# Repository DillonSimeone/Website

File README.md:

# Dillon Simeone | Portfolio & Haptic Lab

A high-performance, modular portfolio showcasing innovation at the intersection of accessibility, haptics, and embedded engineering.

---

## Overview
This repository contains the source code for my portfolio website. More than just a static page, this project is a testbed for extreme performance optimization and modular content management. 

I am a **Deaf engineer, maker, and designer** specializing in haptic feedback systems and accessibility technology. This site reflects that multidisciplinary approach, combining sleek aesthetics with rigorous technical foundations.

### Key Features:
- **Modular Content Architecture**: Projects are managed as standalone HTML fragments in `src/content/`, dynamically injected via Handlebars.
- **Minification**: Powered by Vite and `vite-plugin-singlefile`, the entire production site is bundled into a single, highly-compressed `index.html`.
- **Shop**: A direct-to-maker storefront integrated with Stripe for hardware prototypes and art pieces.
- **Performance-First Background**: Uses static SVG "skeletons" with real-time color re-skinning to achieve 60FPS animations with ~0% CPU overhead.

---

## Tech Stack
- **Core**: HTML5, Vanilla JavaScript, CSS3
- **Build Engine**: [Vite](https://vitejs.dev/)
- **Templating**: Handlebars
- **Plugins**: 
  - `vite-plugin-singlefile`: Inlines all assets into one file for the final build.
  - `vite-plugin-handlebars`: Manages modular content injection and HMR.
  - `vite-plugin-minify`: Strips whitespace, comments, and console logs.
  - `Terser`: Advanced JS compression for production.

---

## Project Structure
- **`src/`**: Source files.
  - **`content/`**: Categorized project cards (`laser/`, `3dprinting/`, `esp32/`, `shop/`).
  - **`partials/`**: Reusable UI components like navigation and the hero section.
  - **`scripts/`**: Modular logic for theme management and animations.
  - **`styles/`**: Centralized CSS with theming variables.
- **`public/`**: Static assets, including mini-projects, images, and research PDFs.
- **`dist/`**: Automated production build output.
- **`legacy/`**: Preservation of original root files and background regeneration tools.

---

## Development

### Prerequisites
- [Node.js](https://nodejs.org/) (Latest LTS)
- NPM

### Commands
```bash
# Install dependencies
npm install

# Start local development server (with HMR)
npm run dev

# Generate production build (dist/index.html)
npm run build
```

### Content Generation
To add a new project or shop entry without manual boilerplate, use the provided utility:
```bash
.\CreateEntry.bat
```
Follow the prompts to select a category, and the script will generate a correctly formatted HTML fragment in the appropriate directory.

---

## Research & Accessibility
A core pillar of this portfolio is my work on the **GeLu (GestoLumina) Bracers** and the **PULSE Haptic Ecosystem**. These projects focus on universal music design and environmental awareness for the Deaf community. 

For more details, see the documentation in the **Work** and **Embedded** sections of the site.

---

## License
© Dillon Simeone. All rights reserved.

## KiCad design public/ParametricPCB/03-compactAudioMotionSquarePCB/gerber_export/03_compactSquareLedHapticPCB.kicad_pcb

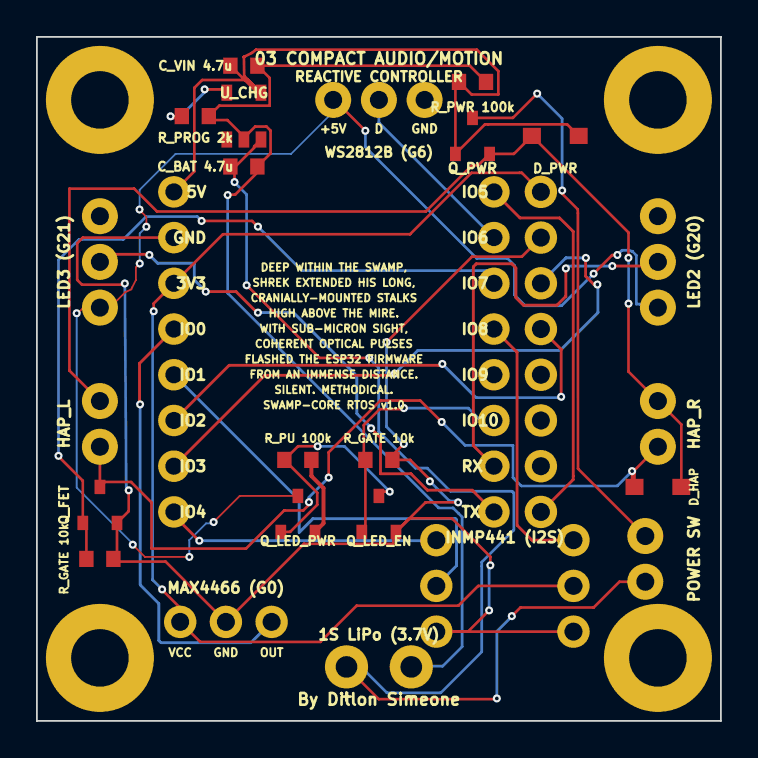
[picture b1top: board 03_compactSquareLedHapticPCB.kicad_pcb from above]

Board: 2 copper layers, 38.0 x 38.0 mm, 25 parts (0 on the bottom side), 24 nets.

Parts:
C_BAT: chip
C_VIN: chip
D_HAP: chip
D_PWR: chip
J_BAT: chip
J_HAP_L: chip
J_HAP_R: chip
J_LED, J_LED2, J_LED3: chip
J_MIC_INMP: chip
J_MIC_MAX: chip
Q_FET: chip
Q_LED_EN: chip
Q_LED_PWR: chip
Q_PWR: chip
R_GATE: chip
R_LED_GATE: chip
R_LED_PU: chip
R_PROG: chip
R_PWR: chip
SW_EXT: chip
U_CHG: chip
U_IMU: chip
U_MCU: chip

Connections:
C_VIN____pin2_to__U_CHG____pin2: C_BAT.2, C_VIN.2, J_BAT.2, R_PROG.2, R_PWR.2, U_CHG.2
D_HAP____pin1_to__J_HAP_L____pin1: D_HAP.1, D_PWR.1, J_HAP_L.1, J_HAP_R.1, Q_PWR.2
Q_FET____pin3_to__J_HAP_L____pin2: D_HAP.2, J_HAP_L.2, J_HAP_R.2, Q_FET.3
Q_LED_EN____pin3_to__Q_LED_PWR____pin1: Q_LED_EN.3, Q_LED_PWR.1, R_LED_PU.1
Q_LED_PWR____pin3_to__J_LED____pin1: J_LED.1, J_LED2.1, J_LED3.1, Q_LED_PWR.3
R_LED_PU____pin2_to__Q_LED_PWR____pin2: Q_LED_PWR.2, R_LED_PU.2
SW_EXT____pin2_to__Q_PWR____pin3: Q_PWR.3, SW_EXT.2
U_CHG____pin3_to__C_BAT____pin1: C_BAT.1, J_BAT.1, SW_EXT.1, U_CHG.3
U_CHG____pin5_to__R_PROG____pin1: R_PROG.1, U_CHG.5
U_MCU____pin1_to__U_CHG____pin4: C_VIN.1, D_PWR.2, Q_PWR.1, R_PWR.1, U_CHG.4, U_MCU.1
U_MCU____pin2_to__U_IMU____pin2: J_MIC_INMP.3, J_MIC_INMP.6, J_MIC_MAX.2, Q_FET.2, Q_LED_EN.2, R_GATE.2, R_LED_GATE.2, U_IMU.2, U_MCU.2
U_MCU____pin3_to__U_IMU____pin1: J_MIC_INMP.5, J_MIC_MAX.1, U_IMU.1, U_MCU.3
U_MCU____pin4_to__J_MIC_MAX____pin3: J_MIC_MAX.3, U_MCU.4
U_MCU____pin5_to__J_MIC_INMP____pin2: J_MIC_INMP.2, U_MCU.5
U_MCU____pin6_to__U_IMU____pin4: U_IMU.4, U_MCU.6
U_MCU____pin7_to__U_IMU____pin3: U_IMU.3, U_MCU.7
U_MCU____pin8_to__J_MIC_INMP____pin1: J_MIC_INMP.1, U_MCU.8
U_MCU____pin9_to__U_IMU____pin8: U_IMU.8, U_MCU.9
U_MCU____pin10_to__J_LED____pin2: J_LED.2, U_MCU.10
U_MCU____pin11_to__Q_FET____pin1: Q_FET.1, R_GATE.1, U_MCU.11
U_MCU____pin12_to__J_MIC_INMP____pin4: J_MIC_INMP.4, U_MCU.12
U_MCU____pin14_to__Q_LED_EN____pin1: Q_LED_EN.1, R_LED_GATE.1, U_MCU.14
U_MCU____pin15_to__J_LED2____pin2: J_LED2.2, U_MCU.15
U_MCU____pin16_to__J_LED3____pin2: J_LED3.2, U_MCU.16

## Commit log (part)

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2026-05-27 Bump tmp and karma
    Bumps [tmp](https://github.com/raszi/node-tmp) to 0.2.6 and updates ancestor dependency [karma](https://github.com/karma-runner/karma). These dependencies need to be updated together.
    Updates `tmp` from 0.2.1 to 0.2.6
    - [Changelog](https://github.com/raszi/node-tmp/blob/master/CHANGELOG.md)
    - [Commits](https://github.com/raszi/node-tmp/compare/v0.2.1...v0.2.6)
    Updates `karma` from 6.2.0 to 6.4.4
    - [Release notes](https://github.com/karma-runner/karma/releases)
2026-05-27 Bump tmp and eslint in /public/Work/Crossroad/scripts/tingle-master
    Removes [tmp](https://github.com/raszi/node-tmp). It's no longer used after updating ancestor dependency [eslint](https://github.com/eslint/eslint). These dependencies need to be updated together.
    Removes `tmp`
    Updates `eslint` from 6.8.0 to 10.4.0
    - [Release notes](https://github.com/eslint/eslint/releases)
    - [Commits](https://github.com/eslint/eslint/compare/v6.8.0...v10.4.0)
    ---
2026-05-28 Update Ember
2026-05-28 The Lighthouse shines
2026-05-28 Lighthouse shining phase two
2026-05-28 Lighthouse Phase 3
2026-05-28 Lighthouse phase 4
2026-05-28 Light house phase 5
2026-05-28 More lighthouse shining
2026-05-29 Bump ws in /public/CyclingMax/AudioProgramming2/project4
    Bumps [ws](https://github.com/websockets/ws) from 8.18.1 to 8.20.1.
    - [Release notes](https://github.com/websockets/ws/releases)
    - [Commits](https://github.com/websockets/ws/compare/8.18.1...8.20.1)
    ---
    updated-dependencies:
    - dependency-name: ws
2026-05-29 Haxel Update
2026-05-30 Scheming
2026-05-31 UpdateCyberDeck
2026-05-31 cyberdeeecccckkkk!
2026-06-01 cyberdeck Update
2026-06-02 KnobsUpdate
2026-06-02 SECURITY PUNCH!
2026-06-03 PunchUpdate
2026-06-03 Mobile support improve
2026-06-06 UpdateModeling
2026-06-08 Update Haxel
2026-06-08 Writing
2026-06-08 EmberUpdate
2026-06-08 More writing
2026-06-09 LightBaton Update
2026-06-09 Perfection
2026-06-10 CleanUp, local mode added
2026-06-10 Retro Client
2026-06-10 Content Manager implemented!
    Just had an eurkua moment for making my website more easily managed!
    https://www.youtube.com/watch?v=nHmx3GNFjgE
    Long story short, my website compresses all of those loose files into one DENSE single file that's hosted on my server. The items appears in my lists in the way they do due to 00, 01, 02, etc next to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
    Just vibecoded up a simple express.js server that auto handle reordering the files by renaming them when I drag things around! This is going to save me a lot of sanity in the long run... I just start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
2026-06-10 Pathing Fix
2026-06-10 typos clean up
2026-06-11 Cleanup
2026-06-11 shrekisalwayswatching
2026-06-12 Updating Updatey
2026-06-12 Clean up, improve models
2026-06-12 Bump esbuild in /public/Work/AugmentedReailityBook/MindAR
    Bumps [esbuild](https://github.com/evanw/esbuild) from 0.27.4 to 0.28.1.
    - [Release notes](https://github.com/evanw/esbuild/releases)
    - [Changelog](https://github.com/evanw/esbuild/blob/main/CHANGELOG.md)
    - [Commits](https://github.com/evanw/esbuild/compare/v0.27.4...v0.28.1)
    ---
    updated-dependencies:
2026-06-13 Bump esbuild and vite
    Removes [esbuild](https://github.com/evanw/esbuild). It's no longer used after updating ancestor dependency [vite](https://github.com/vitejs/vite/tree/HEAD/packages/vite). These dependencies need to 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
    Removes `esbuild`
    Updates `vite` from 5.4.21 to 8.0.16
    - [Release notes](https://github.com/vitejs/vite/releases)
    - [Changelog](https://github.com/vitejs/vite/blob/main/packages/vite/CHANGELOG.md)
    - [Commits](https://github.com/vitejs/vite/commits/v8.0.16/packages/vite)
2026-06-13 JST channel added
2026-06-13 LightBaton
2026-06-14 BurningTokens
2026-06-14 SillyWriting
2026-06-14 Refactor
2026-06-14 UpdateAccessKnobs
2026-06-15 Shattering the glass ceiling
2026-06-15 Styling Fix
2026-06-15 DRY Refactor
2026-06-15 Remove background thrashing
2026-06-15 Improve wrench
2026-06-15 Clean up, big updates
2026-06-15 LLMtokenTracker
2026-06-15 ImproveTokenTracker
2026-06-15 Bump form-data, backstopjs and jest
    Removes [form-data](https://github.com/form-data/form-data). It's no longer used after updating ancestor dependencies [form-data](https://github.com/form-data/form-data), [backstopjs](https://github.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
    Removes `form-data`
    Updates `backstopjs` from 4.4.2 to 6.3.25
    - [Release notes](https://github.com/garris/backstopjs/releases)
    - [Changelog](https://github.com/garris/BackstopJS/blob/master/changelog.md)
    - [Commits](https://github.com/garris/backstopjs/commits)
2026-06-16 Bump vite from 8.0.10 to 8.0.16
    Bumps [vite](https://github.com/vitejs/vite/tree/HEAD/packages/vite) from 8.0.10 to 8.0.16.
    - [Release notes](https://github.com/vitejs/vite/releases)
    - [Changelog](https://github.com/vitejs/vite/blob/main/packages/vite/CHANGELOG.md)
    - [Commits](https://github.com/vitejs/vite/commits/v8.0.16/packages/vite)
    ---
    updated-dependencies:
2026-06-16 Ember Update, ESPtoolpy madness
2026-06-17 Improved tokenTracker
2026-06-17 Fix cache.json
2026-06-17 Bump markdown-it and jsdoc
    Bumps [markdown-it](https://github.com/markdown-it/markdown-it) to 14.2.0 and updates ancestor dependency [jsdoc](https://github.com/jsdoc/jsdoc). These dependencies need to be updated together.
    Updates `markdown-it` from 10.0.0 to 14.2.0
    - [Changelog](https://github.com/markdown-it/markdown-it/blob/master/CHANGELOG.md)
    - [Commits](https://github.com/markdown-it/markdown-it/compare/10.0.0...14.2.0)
    Updates `jsdoc` from 3.6.6 to 4.0.5
    - [Release notes](https://github.com/jsdoc/jsdoc/releases)
2026-06-17 WHO IS IN THE BATHROOM!?
2026-06-17 Who's in the bathroom!?
2026-06-17 Bump webpack-dev-server
    Bumps [webpack-dev-server](https://github.com/webpack/webpack-dev-server) from 3.10.1 to 5.2.5.
    - [Release notes](https://github.com/webpack/webpack-dev-server/releases)
    - [Changelog](https://github.com/webpack/webpack-dev-server/blob/main/CHANGELOG.md)
    - [Commits](https://github.com/webpack/webpack-dev-server/compare/v3.10.1...v5.2.5)
    ---
    updated-dependencies:
2026-06-17 Bump js-yaml and eslint in /public/Work/Crossroad/scripts/tingle-master
    Removes [js-yaml](https://github.com/nodeca/js-yaml). It's no longer used after updating ancestor dependency [eslint](https://github.com/eslint/eslint). These dependencies need to be updated together.
    Removes `js-yaml`
    Updates `eslint` from 6.8.0 to 10.5.0
    - [Release notes](https://github.com/eslint/eslint/releases)
    - [Commits](https://github.com/eslint/eslint/compare/v6.8.0...v10.5.0)
    ---
2026-06-17 Bump @babel/core
    Bumps [@babel/core](https://github.com/babel/babel/tree/HEAD/packages/babel-core) from 7.7.7 to 7.29.6.
    - [Release notes](https://github.com/babel/babel/releases)
    - [Changelog](https://github.com/babel/babel/blob/main/CHANGELOG.md)
    - [Commits](https://github.com/babel/babel/commits/v7.29.6/packages/babel-core)
    ---
    updated-dependencies:
2026-06-17 Bump markdown-it in /public/Work/AugmentedReailityBook/MindAR
    Bumps [markdown-it](https://github.com/markdown-it/markdown-it) from 14.1.1 to 14.2.0.
    - [Changelog](https://github.com/markdown-it/markdown-it/blob/master/CHANGELOG.md)
    - [Commits](https://github.com/markdown-it/markdown-it/compare/14.1.1...14.2.0)
    ---
    updated-dependencies:
    - dependency-name: markdown-it
2026-06-18 Update Light Baton
2026-06-19 Fix background crash
2026-06-19 geocities!
2026-06-20 Hints to V2.0
2026-06-21 Clean-up, PIO web uploader
2026-06-22 MIT added!
2026-06-22 Reorganizing folders
2026-06-22 Old links now points to new links
2026-06-22 Purge emotions
2026-06-22 Update video elements, fixed UMD post.
2026-06-23 Fix ESP32 links, working on new model
2026-06-23 Cylinder Caps - Accepts any sheets!
2026-06-23 Nearly perfected sheet to tube defaults
2026-06-24 Modularizing - I should have been doing that all along!
2026-06-24 Improved exporter
2026-06-26 Moldularizing
2026-06-26 We like to eat glue
2026-06-27 Improvements on Pots
2026-06-27 This machine destroys facism
2026-06-27 Improved Text Generation
2026-06-27 Slogan generator!
2026-06-27 Slogan everything!
2026-06-27 Footprint updated, DRC added
2026-06-28 More modularizing work, polish and writing
2026-06-28 Haxel improvements
    BEWARE, TracyEdit was tainted by Adobe on Tracy's side!
2026-06-29 Modularize wrenches and improvements
2026-06-29 PosterUpdate
2026-06-29 Fix wrenches, update poster
2026-06-30 AccessKnobs
2026-06-30 Laser cutter fix
